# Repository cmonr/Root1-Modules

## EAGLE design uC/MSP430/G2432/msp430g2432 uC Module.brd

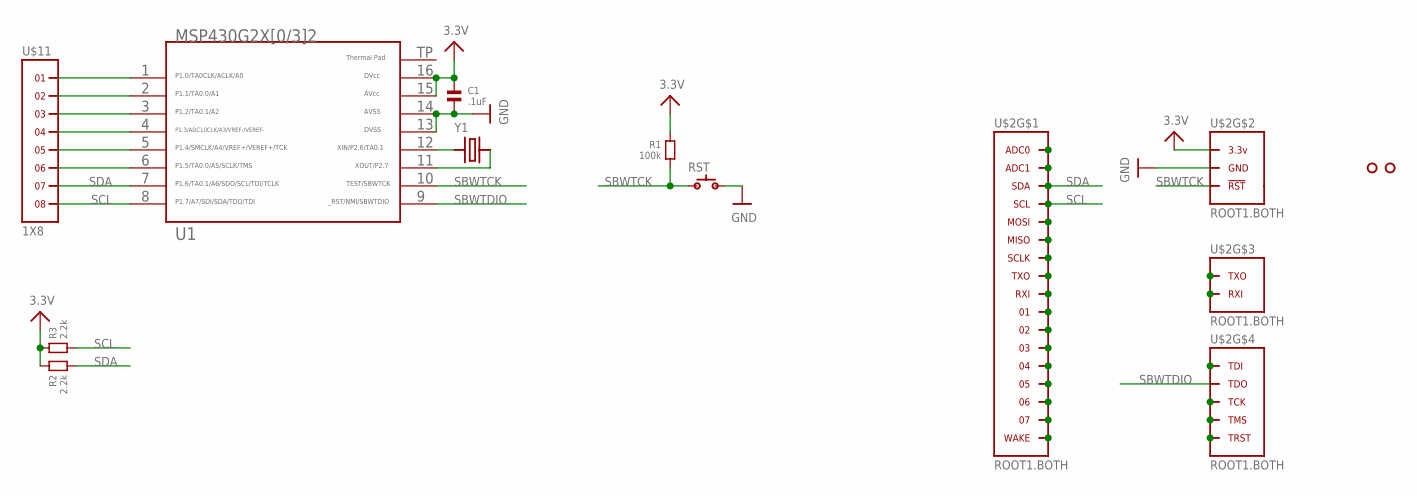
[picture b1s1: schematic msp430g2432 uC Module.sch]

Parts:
C1: .1uF; 0603
R1: 100k; 0603
R2, R3: 2.2k; 0603
RST: SPST.B3U-3000P(M)-B; B3U-3000P(M)-B
U1: G2432.QFN16; RSA16
U$2: ROOT1.BOTH
U$3, U$4: HOLE.2MM; 2MM
U$11: 1X8
Y1: CRYSTAL.ABS07; ABS07

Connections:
3.3V: C1.1, R1.1, R2.1, R3.1, U1.15, U1.16, U$2.3.3V@1 (3.3V), U$2.3.3V@2 (3.3V), U$2.3.3V@3 (3.3V), U$2.3.3V@4 (3.3V), U$2.3.3V@5 (3.3V), U$2.3.3V@6 (3.3V), U$2.3.3V@7 (3.3V), U$2.3.3V@8 (3.3V), U$2.3.3V@9 (3.3V), U$2.3.3V@10 (3.3V), U$2.3.3V@11 (3.3V), U$2.3.3V@12 (3.3V), U$2.3.3V@13 (3.3V), U$2.3.3V@14 (3.3V), U$2.3.3V@15 (3.3V), U$2.3.3V@16 (3.3V), U$2.3.3V@17 (3.3V), U$2.3.3V@18 (3.3V), U$2.3.3V@19 (3.3V), U$2.3.3V@20 (3.3V), U$2.3.3V@21 (3.3V), U$2.3.3V@22 (3.3V), U$2.3.3V@23 (3.3V), U$2.3.3V@24 (3.3V), U$2.3.3V@VIA (3.3V)
GND: C1.2, RST.1, U1.13, U1.14, U$2.GND@1 (GND), U$2.GND@2 (GND), U$2.GND@3 (GND), U$2.GND@4 (GND), U$2.GND@5 (GND), U$2.GND@6 (GND), U$2.GND@7 (GND), U$2.GND@8 (GND), U$2.GND@9 (GND), U$2.GND@10 (GND), U$2.GND@11 (GND), U$2.GND@12 (GND), U$2.GND@13 (GND), U$2.GND@14 (GND), U$2.GND@15 (GND), U$2.GND@16 (GND), U$2.GND@17 (GND), U$2.GND@18 (GND), U$2.GND@19 (GND), U$2.GND@20 (GND), U$2.GND@21 (GND), U$2.GND@22 (GND), U$2.GND@23 (GND), U$2.GND@24 (GND), U$2.GND@25 (GND), U$2.GND@26 (GND), U$2.GND@VIA (GND)
unnamed: U$2.04, U$2.04@1 (04), U$2.04@VIA (04)
unnamed: U$2.ADC1, U$2.ADC1@1 (ADC1), U$2.ADC1@VIA (ADC1)
unnamed: U1.1, U$11.1
unnamed: U1.2, U$11.2
unnamed: U$2.03, U$2.03@1 (03), U$2.03@VIA (03)
unnamed: U$2.MISO, U$2.MISO@1 (MISO), U$2.MISO@VIA (MISO)
unnamed: U$2.SCLK, U$2.SCLK@1 (SCLK), U$2.SCLK@VIA (SCLK)
unnamed: U$2.TXO, U$2.TXO@1 (TXO), U$2.TXO@VIA (TXO)
unnamed: U$2.RXI, U$2.RXI@1 (RXI), U$2.RXI@VIA (RXI)
unnamed: U$2.01, U$2.01@1 (01), U$2.01@VIA (01)
unnamed: U$2.02, U$2.02@1 (02), U$2.02@VIA (02)
unnamed: U$2.MOSI, U$2.MOSI@1 (MOSI), U$2.MOSI@VIA (MOSI)
unnamed: U$2.ADC0, U$2.ADC0@1 (ADC0), U$2.ADC0@VIA (ADC0)
unnamed: U$2.05, U$2.05@1 (05), U$2.05@VIA (05)
unnamed: U$2.06, U$2.06@1 (06), U$2.06@VIA (06)
unnamed: U$2.07, U$2.07@1 (07), U$2.07@VIA (07)
unnamed: U$2.WAKE, U$2.WAKE@1 (WAKE), U$2.WAKE@VIA (WAKE)
unnamed: U$2.TDI, U$2.TDI@1 (TDI), U$2.TDI@VIA (TDI)
unnamed: U1.3, U$11.3
unnamed: U1.4, U$11.4
unnamed: U$2.TMS, U$2.TMS@1 (TMS), U$2.TMS@VIA (TMS)
unnamed: U$2.TRST, U$2.TRST@1 (TRST), U$2.TRST@VIA (TRST)
unnamed: U$2.RXI.DBG (RXI), U$2.RXI.DBG@1 (RXI), U$2.RXI.DBG@VIA (RXI)
unnamed: U$2.TXO.DBG (TXO), U$2.TXO.DBG@1 (TXO), U$2.TXO.DBG@VIA (TXO)
unnamed: U1.12, Y1.1
unnamed: U1.11, Y1.2
unnamed: U1.5, U$11.5
unnamed: U1.6, U$11.6
unnamed: U$2.TCK, U$2.TCK@1 (TCK), U$2.TCK@VIA (TCK)
SBWTCK: R1.2, RST.2, U1.10, U$2.RST (!RST), U$2.RST@1 (!RST), U$2.RST@VIA (!RST)
SBWTDIO: U1.9, U$2.TDO, U$2.TDO@1 (TDO), U$2.TDO@VIA (TDO)
SCL: R3.2, U1.8, U$2.SCL, U$2.SCL@1 (SCL), U$2.SCL@VIA (SCL), U$11.8
SDA: R2.2, U1.7, U$2.SDA, U$2.SDA@1 (SDA), U$2.SDA@VIA (SDA), U$11.7

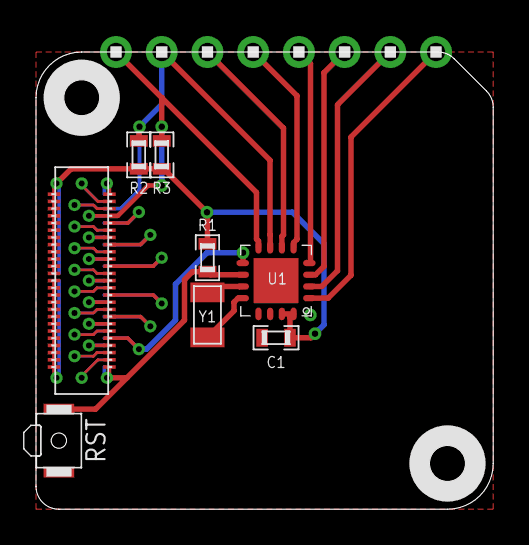
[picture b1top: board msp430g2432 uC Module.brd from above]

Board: 2 copper layers, 25.4 x 25.4 mm, 11 parts (0 on the bottom side), 35 nets.

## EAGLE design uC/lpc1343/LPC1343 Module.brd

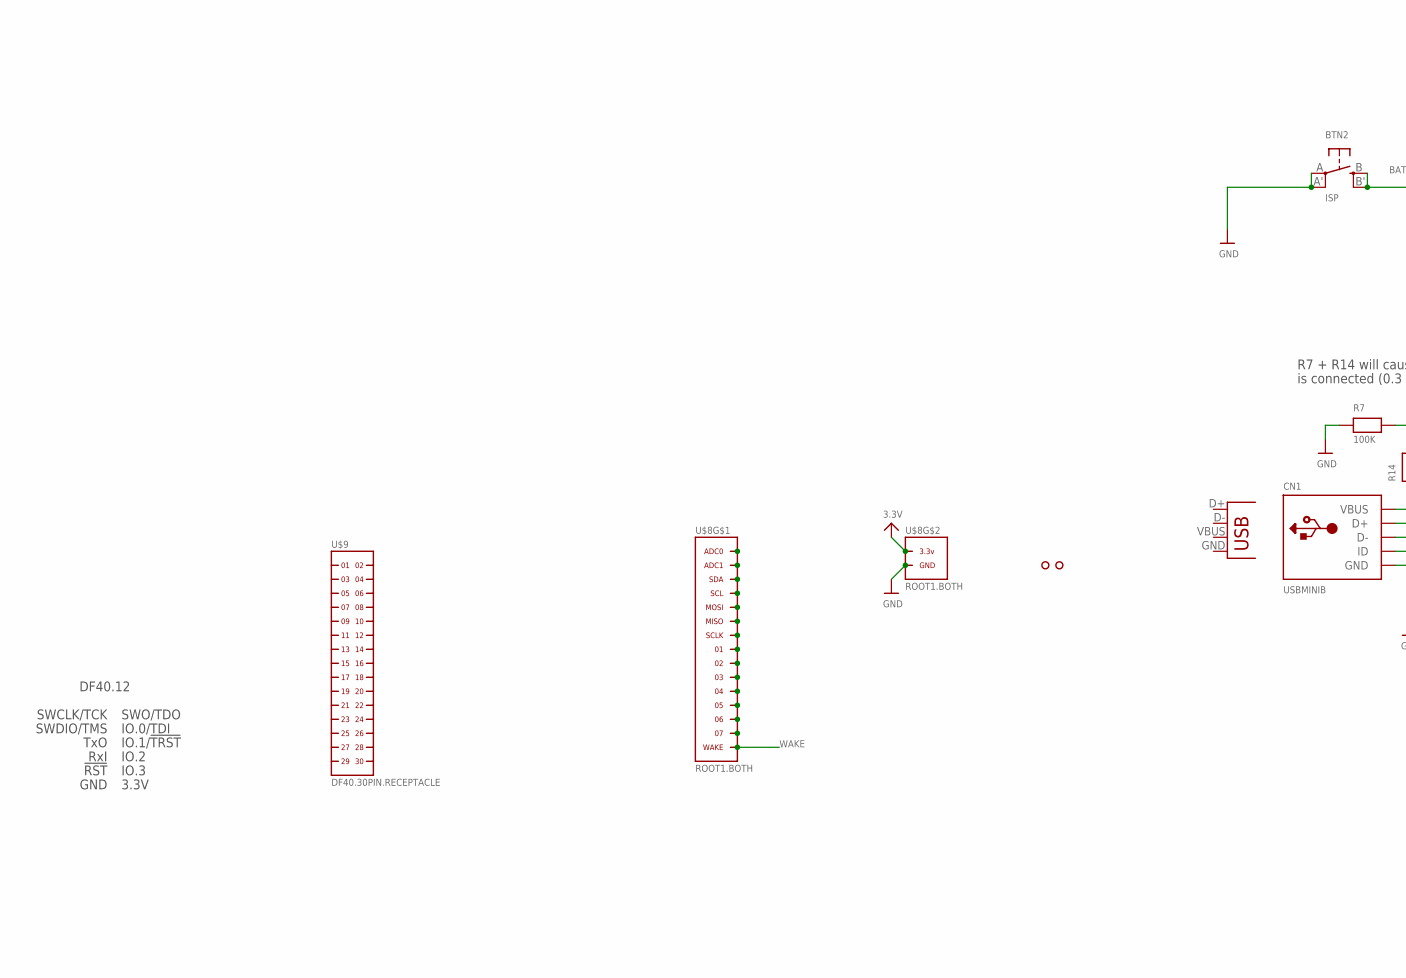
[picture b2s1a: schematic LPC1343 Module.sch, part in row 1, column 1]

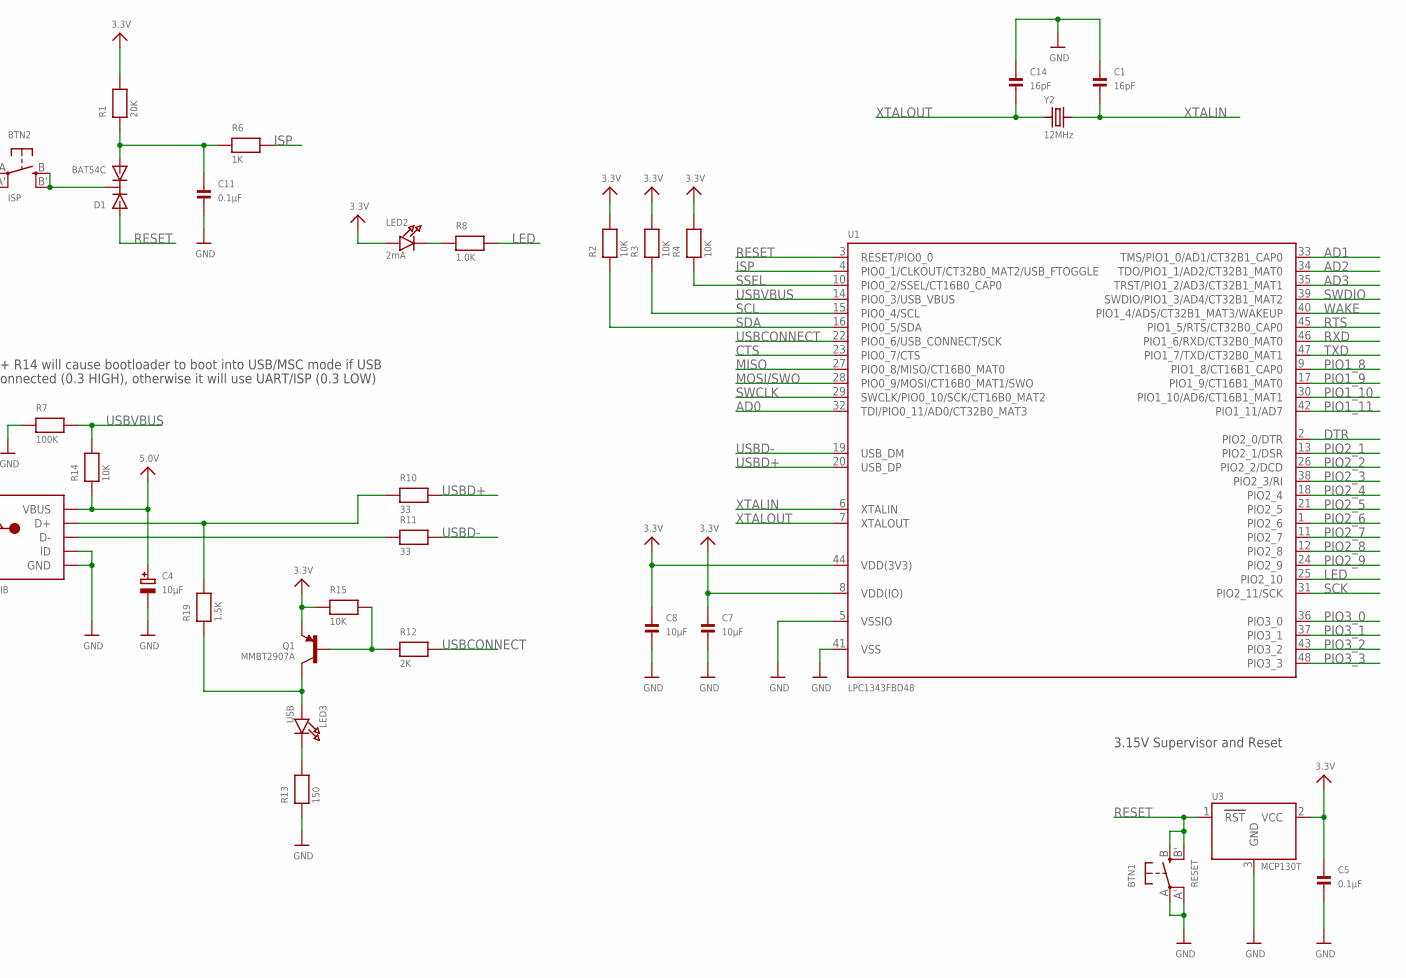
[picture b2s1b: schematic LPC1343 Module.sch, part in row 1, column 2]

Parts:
BTN1: RESET; EVQ-Q2
BTN2: ISP; EVQ-Q2
C1, C14: 16pF; 0603
C4: 10µF; EIA3216-18/A-R
C5, C11: 0.1µF; 0603
C7, C8: 10µF; 0805
CN1: USBMINIB; USB-MINIB
D1: BAT54C; SOT23-R
LED2: 2mA; CHIPLED_0805
LED3: USB; CHIPLED_0805
Q1: MMBT2907A; SOT23-R
R1: 20K; 0603
R2, R3, R4, R14, R15: 10K; 0603
R6: 1K; 0603
R7: 100K; 0603
R8: 1.0K; 0603
R10, R11: 33; 0603
R12: 2K; 0603
R13: 150; 0603
R19: 1.5K; 0603
U1: LPC1343FBD48; LQFP48
U3: MCP130T; SOT23-R
U$3, U$4: HOLE.2MM; 2MM
U$8: ROOT1.BOTH
U$9: DF40.30PIN.RECEPTACLE; DF40(XX)-30DS-0.4V
X1: USB-MICROB
Y2: 12MHz; CRYSTAL_3.2X2.5

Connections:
3.3V: C5.1, C7.1, C8.1, LED2.A, Q1.2 (E), R1.2, R2.2, R3.2, R4.2, R15.1, U1.8 (VDD(IO)), U1.44 (VDD(3V3)), U3.2 (VCC), U$8.3.3V@1 (3.3V), U$8.3.3V@2 (3.3V), U$8.3.3V@3 (3.3V), U$8.3.3V@4 (3.3V), U$8.3.3V@5 (3.3V), U$8.3.3V@6 (3.3V), U$8.3.3V@7 (3.3V), U$8.3.3V@8 (3.3V), U$8.3.3V@9 (3.3V), U$8.3.3V@10 (3.3V), U$8.3.3V@VIA (3.3V)
5.0V: C4.+, CN1.VBUS, R14.1
AD0: U1.32 (TDI/PIO0_11/AD0/CT32B0_MAT3)
AD1: U1.33 (TMS/PIO1_0/AD1/CT32B1_CAP0)
AD2: U1.34 (TDO/PIO1_1/AD2/CT32B1_MAT0)
AD3: U1.35 (TRST/PIO1_2/AD3/CT32B1_MAT1)
CTS: U1.23 (PIO0_7/CTS)
DTR: U1.2 (PIO2_0/DTR)
GND: BTN1.A, BTN1.A' (P1), BTN2.A, BTN2.A' (P1), C1.1, C4.-, C5.2, C7.2, C8.2, C11.2, C14.1, CN1.GND, CN1.ID, R7.1, R13.1, U1.5 (VSSIO), U1.41 (VSS), U3.3 (GND), U$8.GND@1 (GND), U$8.GND@2 (GND), U$8.GND@3 (GND), U$8.GND@4 (GND), U$8.GND@5 (GND), U$8.GND@6 (GND), U$8.GND@7 (GND), U$8.GND@8 (GND), U$8.GND@9 (GND), U$8.GND@10 (GND), U$8.GND@11 (GND), U$8.GND@12 (GND), U$8.GND@13 (GND), U$8.GND@14 (GND), U$8.GND@15 (GND), U$8.GND@16 (GND), U$8.GND@17 (GND), U$8.GND@18 (GND), U$8.GND@19 (GND), U$8.GND@20 (GND), U$8.GND@VIA (GND)
ISP: R6.2, U1.4 (PIO0_1/CLKOUT/CT32B0_MAT2/USB_FTOGGLE)
LED: R8.2, U1.25 (PIO2_10)
MISO: U1.27 (PIO0_8/MISO/CT16B0_MAT0)
MOSI/SWO: U1.28 (PIO0_9/MOSI/CT16B0_MAT1/SWO)
unnamed: U$8.ADC0, U$8.ADC0@1 (ADC0), U$8.ADC0@VIA (ADC0)
unnamed: U$8.ADC1, U$8.ADC1@1 (ADC1), U$8.ADC1@VIA (ADC1)
unnamed: U$8.SDA, U$8.SDA@1 (SDA), U$8.SDA@VIA (SDA)
unnamed: U$8.SCL, U$8.SCL@1 (SCL), U$8.SCL@VIA (SCL)
unnamed: U$8.MOSI, U$8.MOSI@1 (MOSI), U$8.MOSI@VIA (MOSI)
unnamed: U$8.MISO, U$8.MISO@1 (MISO), U$8.MISO@VIA (MISO)
unnamed: U$8.SCLK, U$8.SCLK@1 (SCLK), U$8.SCLK@VIA (SCLK)
unnamed: U$8.01, U$8.01@1 (01), U$8.01@VIA (01)
unnamed: U$8.02, U$8.02@1 (02), U$8.02@VIA (02)
unnamed: U$8.03, U$8.03@1 (03), U$8.03@VIA (03)
unnamed: U$8.04, U$8.04@1 (04), U$8.04@VIA (04)
unnamed: U$8.05, U$8.05@1 (05), U$8.05@VIA (05)
unnamed: U$8.06, U$8.06@1 (06), U$8.06@VIA (06)
unnamed: U$8.07, U$8.07@1 (07), U$8.07@VIA (07)
unnamed: LED2.C, R8.1
unnamed: Q1.1 (B), R12.1, R15.2
unnamed: LED3.C, R13.2
unnamed: LED3.A, Q1.3 (C), R19.1
unnamed: CN1.D-, R11.1
unnamed: CN1.D+, R10.1, R19.2
unnamed: BTN2.B (S), BTN2.B' (S1), D1.3 (C)
unnamed: C11.1, D1.2 (A2), R1.1, R6.1
PIO1_8: U1.9 (PIO1_8/CT16B1_CAP0)
PIO1_9: U1.17 (PIO1_9/CT16B1_MAT0)
PIO1_10: U1.30 (PIO1_10/AD6/CT16B1_MAT1)
PIO1_11: U1.42 (PIO1_11/AD7)
PIO2_1: U1.13 (PIO2_1/DSR)
PIO2_2: U1.26 (PIO2_2/DCD)
PIO2_3: U1.38 (PIO2_3/RI)
PIO2_4: U1.18 (PIO2_4)
PIO2_5: U1.21 (PIO2_5)
PIO2_6: U1.1 (PIO2_6)
PIO2_7: U1.11 (PIO2_7)
PIO2_8: U1.12 (PIO2_8)
PIO2_9: U1.24 (PIO2_9)
PIO3_0: U1.36 (PIO3_0)
PIO3_1: U1.37 (PIO3_1)
PIO3_2: U1.43 (PIO3_2)
PIO3_3: U1.48 (PIO3_3)
RESET: BTN1.B (S), BTN1.B' (S1), D1.1 (A1), U1.3 (RESET/PIO0_0), U3.1 (RST)
RTS: U1.45 (PIO1_5/RTS/CT32B0_CAP0)
RXD: U1.46 (PIO1_6/RXD/CT32B0_MAT0)
SCK: U1.31 (PIO2_11/SCK)
SCL: R3.1, U1.15 (PIO0_4/SCL)
SDA: R2.1, U1.16 (PIO0_5/SDA)
SSEL: R4.1, U1.10 (PIO0_2/SSEL/CT16B0_CAP0)
SWCLK: U1.29 (SWCLK/PIO0_10/SCK/CT16B0_MAT2)
SWDIO: U1.39 (SWDIO/PIO1_3/AD4/CT32B1_MAT2)
TXD: U1.47 (PIO1_7/TXD/CT32B0_MAT1)
USBCONNECT: R12.2, U1.22 (PIO0_6/USB_CONNECT/SCK)
USBD+: R10.2, U1.20 (USB_DP)
USBD-: R11.2, U1.19 (USB_DM)
USBVBUS: R7.2, R14.2, U1.14 (PIO0_3/USB_VBUS)
WAKE: U1.40 (PIO1_4/AD5/CT32B1_MAT3/WAKEUP), U$8.WAKE, U$8.WAKE@1 (WAKE), U$8.WAKE@VIA (WAKE)
XTALIN: C1.2, U1.6 (XTALIN), Y2.2
XTALOUT: C14.2, U1.7 (XTALOUT), Y2.1

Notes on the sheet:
3.15V Supervisor and Reset
R7 + R14 will cause bootloader to boot into USB/MSC mode if USB
is connected (0.3 HIGH), otherwise it will use UART/ISP (0.3 LOW)
DF40.12
SWCLK/TCK
SWDIO/TMS
SWO/TDO
IO.0/TDI
IO.1/!TRST
GND
3.3V
TxO
RxI
!RST
IO.2
IO.3

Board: 2 copper layers, 36 parts (0 on the bottom side), 38 nets, no tracks yet.

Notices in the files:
parts and their libraries:
SparkFun: Licensing: CC v3.0 Share-Alike You are welcome to use this library for commercial purposes.
